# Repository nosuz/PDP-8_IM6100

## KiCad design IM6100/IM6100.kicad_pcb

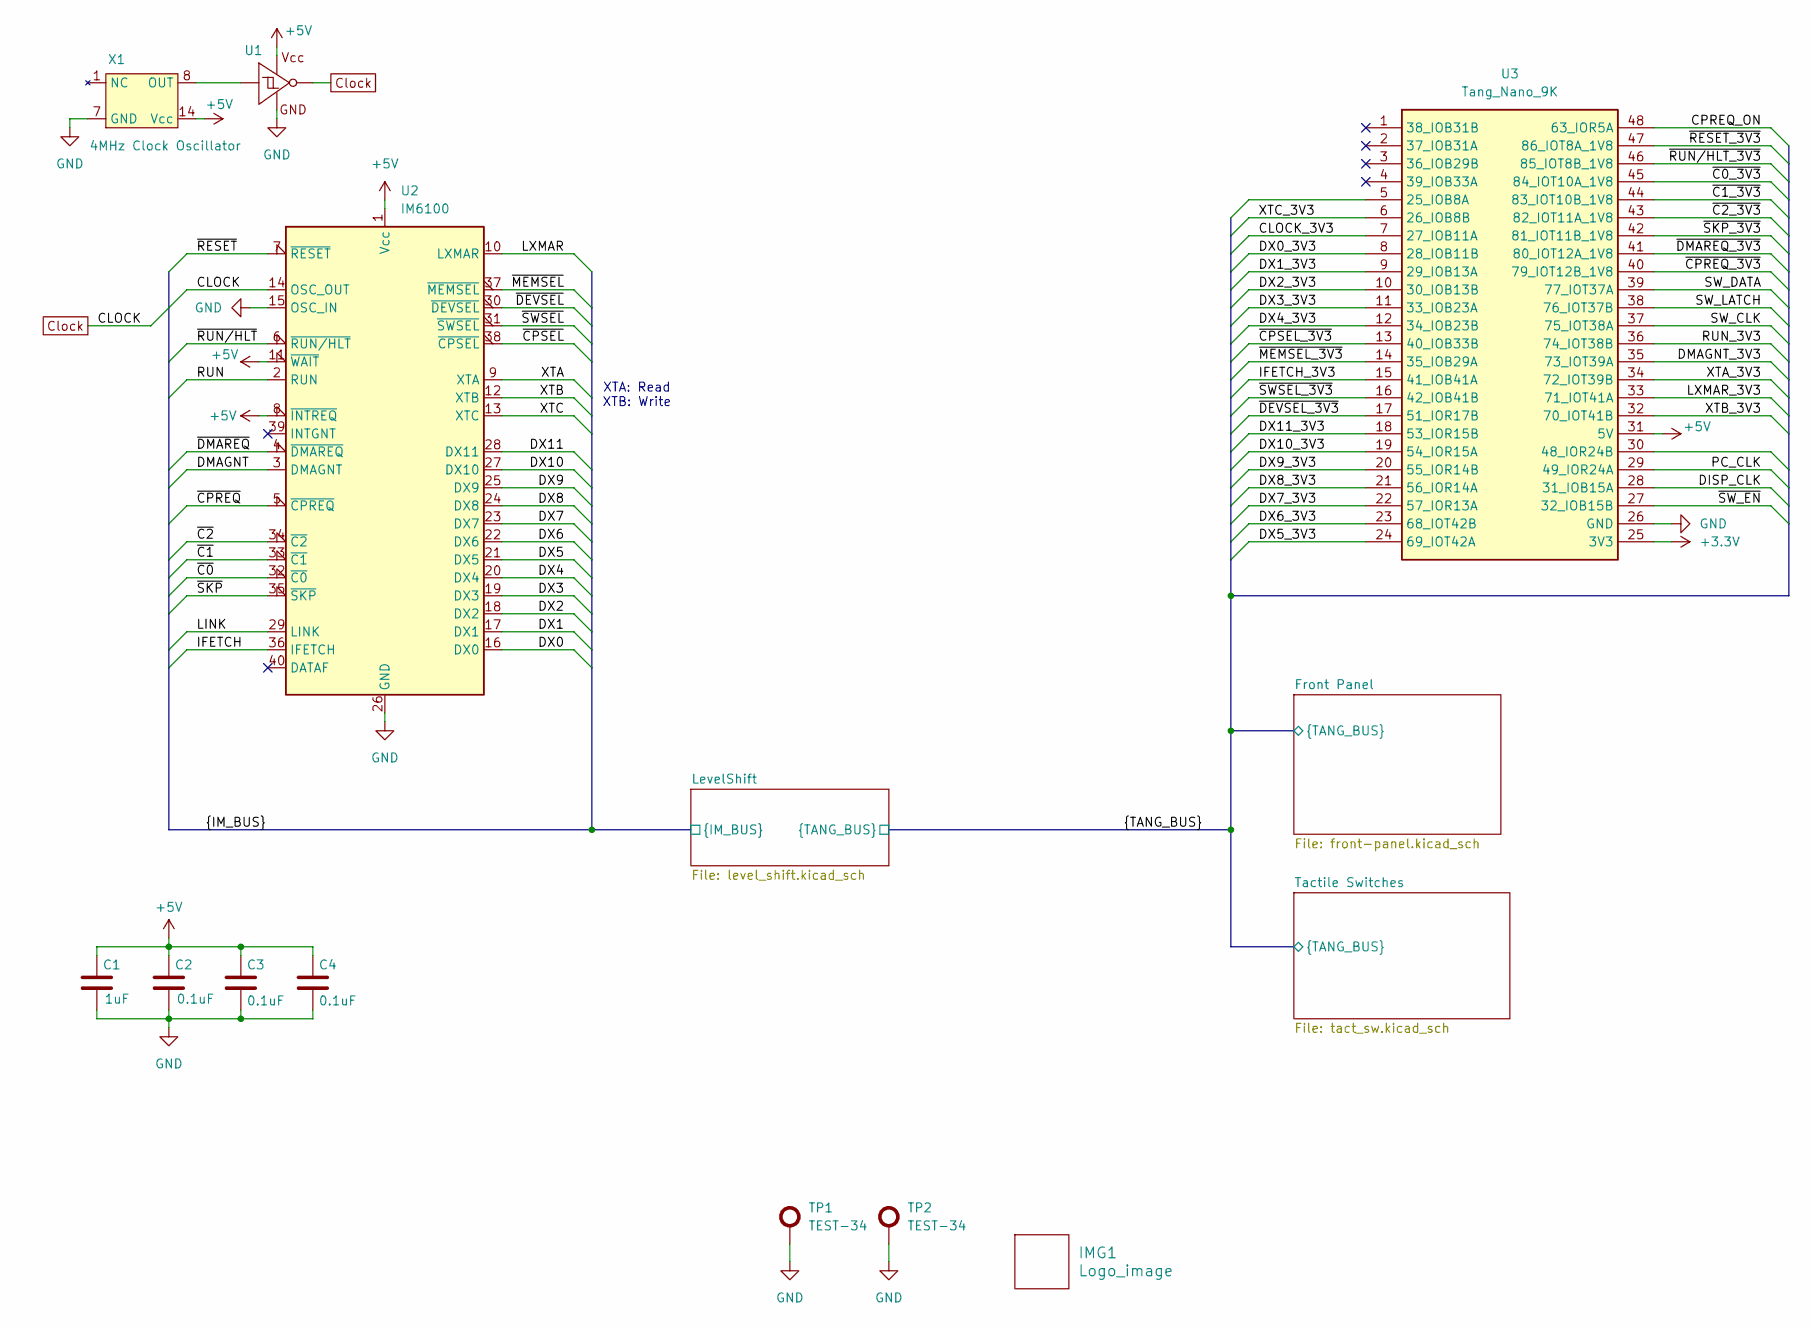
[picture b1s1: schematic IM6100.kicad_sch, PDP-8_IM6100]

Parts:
C1: 1uF; C_1608_0603; LCSC C15849
C2, C3, C4: 0.1uF; C_1608_0603; LCSC C14663
IMG1: Logo_image; Icon_Nosuz
TP1, TP2: TEST-34
U1: SN74AHCT1G14DBV; SOT-23-5_TI; LCSC C55250
U2: IM6100; DIP-40_IM6100
U3: Tang_Nano_9K; DIP-48_TangNano9K
X1: 4MHz Clock Oscillator; DIP-14_ClockOscillator

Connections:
+3.3V: U3.25 (3V3); also elsewhere on the board
+5V: C1.1, C2.1, C3.1, C4.1, U1.5 (Vcc), U2.1 (Vcc), U2.8 (~INTREQ), U2.11 (~WAIT), U3.31 (5V), X1.11 (Vcc), X1.14 (Vcc); also elsewhere on the board
/CLOCK_3V3: U3.7 (27_IOB11A); also elsewhere on the board
/CPREQ_ON: U3.48 (63_IOR5A); also elsewhere on the board
/DISP_CLK: U3.28 (31_IOB15A); also elsewhere on the board
/DMAGNT: U2.3 (DMAGNT); also elsewhere on the board
/DMAGNT_3V3: U3.35 (73_IOT39A); also elsewhere on the board
/DX0: U2.16 (DX0); also elsewhere on the board
/DX0_3V3: U3.8 (28_IOB11B); also elsewhere on the board
/DX1: U2.17 (DX1); also elsewhere on the board
/DX1_3V3: U3.9 (29_IOB13A); also elsewhere on the board
/DX2: U2.18 (DX2); also elsewhere on the board
/DX2_3V3: U3.10 (30_IOB13B); also elsewhere on the board
/DX3: U2.19 (DX3); also elsewhere on the board
/DX3_3V3: U3.11 (33_IOB23A); also elsewhere on the board
/DX4: U2.20 (DX4); also elsewhere on the board
/DX4_3V3: U3.12 (34_IOB23B); also elsewhere on the board
/DX5: U2.21 (DX5); also elsewhere on the board
/DX5_3V3: U3.24 (69_IOT42A); also elsewhere on the board
/DX6: U2.22 (DX6); also elsewhere on the board
/DX6_3V3: U3.23 (68_IOT42B); also elsewhere on the board
/DX7: U2.23 (DX7); also elsewhere on the board
/DX7_3V3: U3.22 (57_IOR13A); also elsewhere on the board
/DX8: U2.24 (DX8); also elsewhere on the board
/DX8_3V3: U3.21 (56_IOR14A); also elsewhere on the board
/DX9: U2.25 (DX9); also elsewhere on the board
/DX9_3V3: U3.20 (55_IOR14B); also elsewhere on the board
/DX10: U2.27 (DX10); also elsewhere on the board
/DX10_3V3: U3.19 (54_IOR15A); also elsewhere on the board
/DX11: U2.28 (DX11); also elsewhere on the board
/DX11_3V3: U3.18 (53_IOR15B); also elsewhere on the board
/IFETCH: U2.36 (IFETCH); also elsewhere on the board
/IFETCH_3V3: U3.15 (41_IOB41A); also elsewhere on the board
/LINK: U2.29 (LINK); also elsewhere on the board
/LXMAR: U2.10 (LXMAR); also elsewhere on the board
/LXMAR_3V3: U3.33 (71_IOT41A); also elsewhere on the board
/PC_CLK: U3.29 (49_IOR24A); also elsewhere on the board
/RUN: U2.2 (RUN); also elsewhere on the board
/RUN_3V3: U3.36 (74_IOT38B); also elsewhere on the board
/SW_CLK: U3.37 (75_IOT38A); also elsewhere on the board
/SW_DATA: U3.39 (77_IOT37A); also elsewhere on the board
/SW_LATCH: U3.38 (76_IOT37B); also elsewhere on the board
/XTA: U2.9 (XTA); also elsewhere on the board
/XTA_3V3: U3.34 (72_IOT39B); also elsewhere on the board
/XTB: U2.12 (XTB); also elsewhere on the board
/XTB_3V3: U3.32 (70_IOT41B); also elsewhere on the board
/XTC: U2.13 (XTC); also elsewhere on the board
/XTC_3V3: U3.6 (26_IOB8B); also elsewhere on the board
/~C0_3V3: U3.45 (84_IOT10A_1V8); also elsewhere on the board
/~C0: U2.32 (~C0); also elsewhere on the board
/~C1_3V3: U3.44 (83_IOT10B_1V8); also elsewhere on the board
/~C1: U2.33 (~C1); also elsewhere on the board
/~C2_3V3: U3.43 (82_IOT11A_1V8); also elsewhere on the board
/~C2: U2.34 (~C2); also elsewhere on the board
/~CPREQ_3V3: U3.40 (79_IOT12B_1V8); also elsewhere on the board
/~CPREQ: U2.5 (~CPREQ); also elsewhere on the board
/~CPSEL_3V3: U3.13 (40_IOB33B); also elsewhere on the board
/~CPSEL: U2.38 (~CPSEL); also elsewhere on the board
/~DEVSEL_3V3: U3.17 (51_IOR17B); also elsewhere on the board
/~DEVSEL: U2.30 (~DEVSEL); also elsewhere on the board
/~DMAREQ_3V3: U3.41 (80_IOT12A_1V8); also elsewhere on the board
/~DMAREQ: U2.4 (~DMAREQ); also elsewhere on the board
/~MEMSEL_3V3: U3.14 (35_IOB29A); also elsewhere on the board
/~MEMSEL: U2.37 (~MEMSEL); also elsewhere on the board
/~RESET_3V3: U3.47 (86_IOT8A_1V8); also elsewhere on the board
/~RESET: U2.7 (~RESET); also elsewhere on the board
/~RUN/HLT_3V3: U3.46 (85_IOT8B_1V8); also elsewhere on the board
/~RUN/HLT: U2.6 (~RUN/HLT); also elsewhere on the board
/~SKP_3V3: U3.42 (81_IOT11B_1V8); also elsewhere on the board
/~SKP: U2.35 (~SKP); also elsewhere on the board
/~SWSEL_3V3: U3.16 (42_IOB41B); also elsewhere on the board
/~SWSEL: U2.31 (~SWSEL); also elsewhere on the board
/~SW_EN: U3.27 (32_IOB15B); also elsewhere on the board
Clock: U1.4 (Y), U2.14 (OSC_OUT); also elsewhere on the board
GND: C1.2, C2.2, C3.2, C4.2, TP1.1 (Test), TP2.1 (Test), U1.3 (GND), U2.15 (OSC_IN), U2.26 (GND), U3.26 (GND), X1.2 (GND), X1.3 (GND), X1.5 (GND), X1.6 (GND), X1.7 (GND), X1.9 (GND), X1.10 (GND), X1.12 (GND), X1.13 (GND); also elsewhere on the board
unnamed: U1.2 (A), X1.8 (OUT)

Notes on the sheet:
XTA: Read XTB: Write

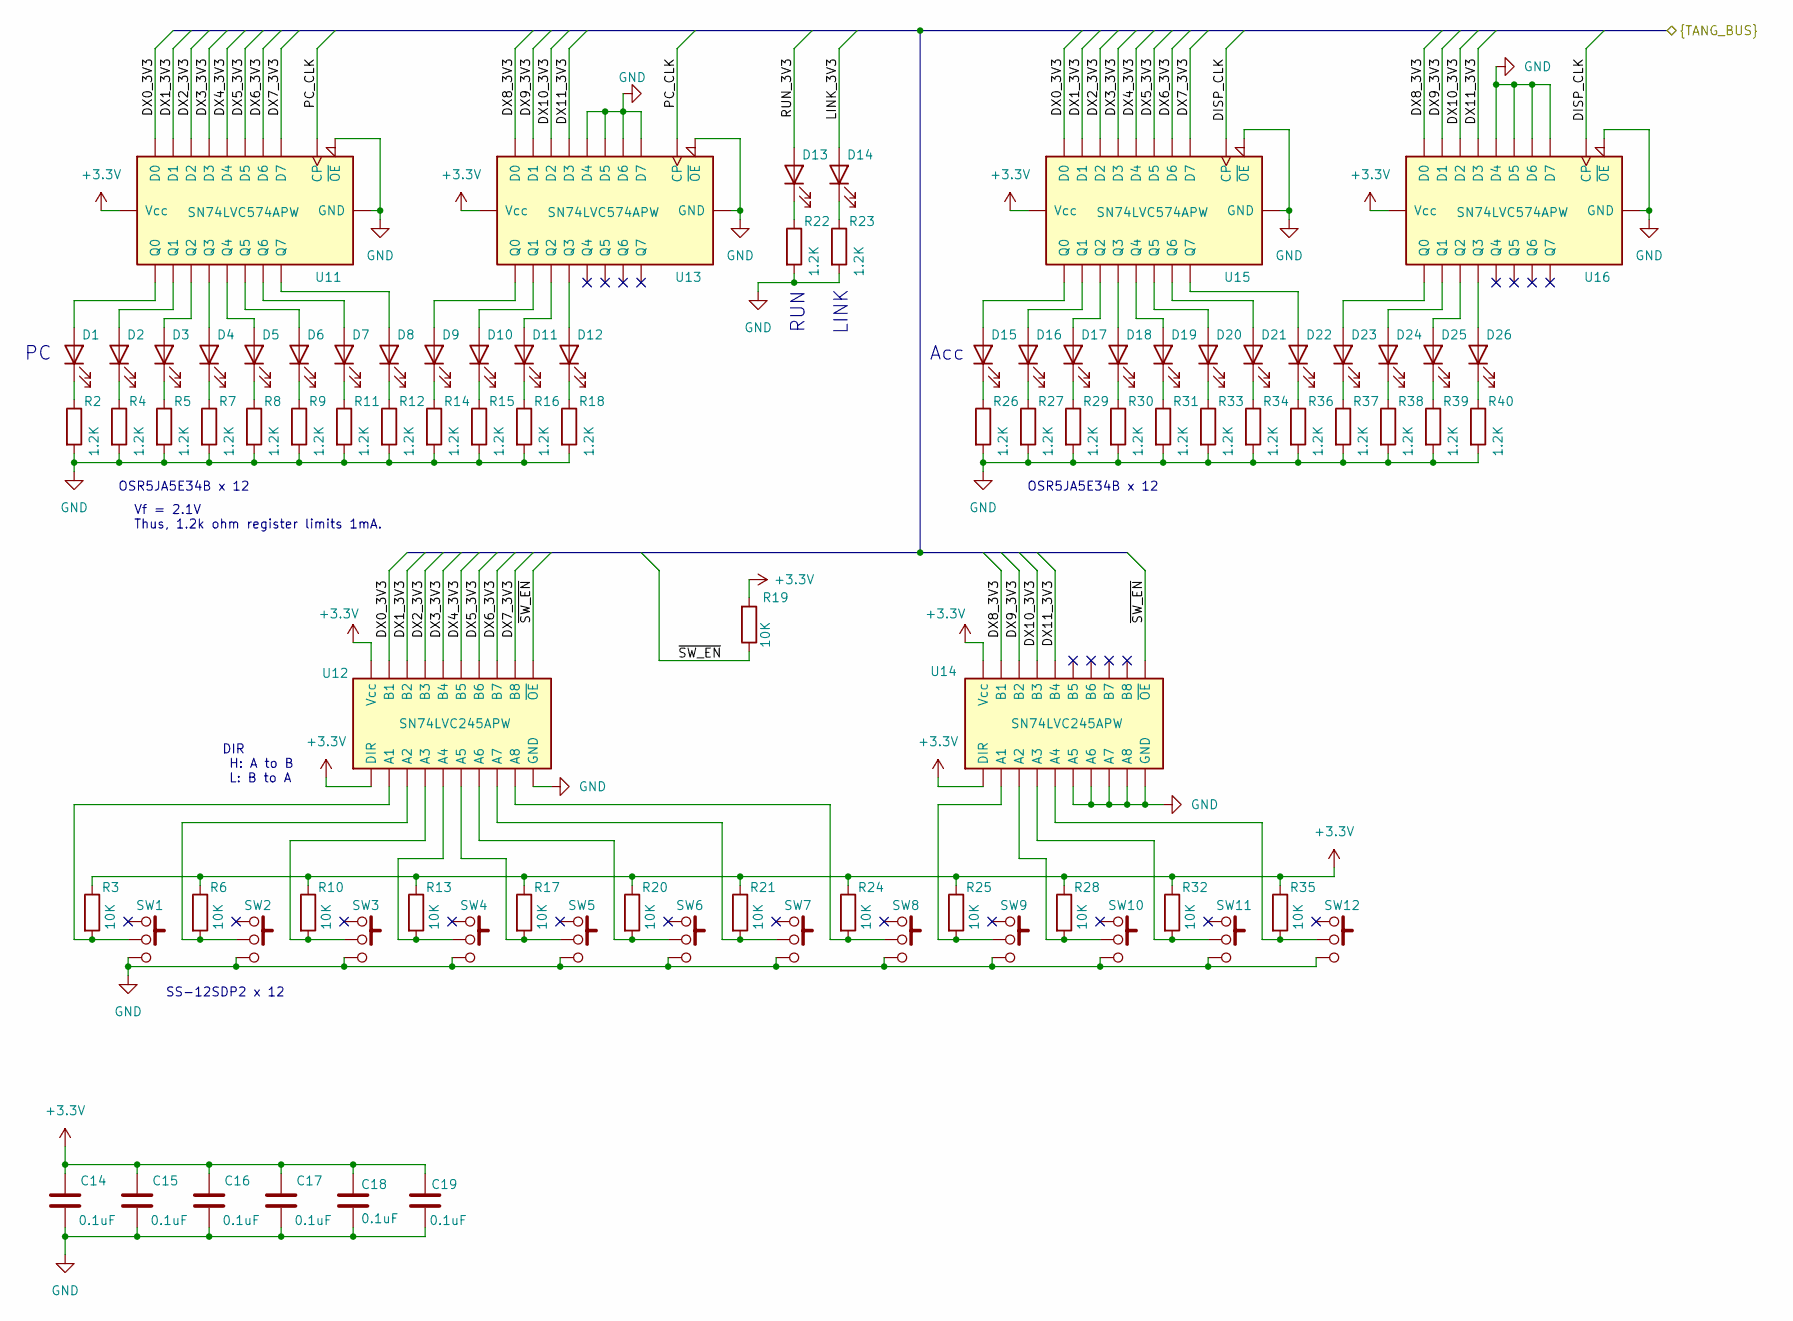
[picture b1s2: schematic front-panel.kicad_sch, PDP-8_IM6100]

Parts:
C14, C15, C16, C17, C18, C19: 0.1uF; C_1608_0603; LCSC C14663
D1, D2, D3, D4, D5, D6, D7, D8, D9, D10, D11, D12, D13, D14, D15, D16, D17, D18, D19, D20, D21, D22, D23, D24, D25, D26: OSR5JA5E34B; LED_5mm
R2, R4, R5, R7, R8, R9, R11, R12, R14, R15, R16, R18, R22, R23, R26, R27, R29, R30, R31, R33, R34, R36, R37, R38, R39, R40: 1.2K; R_1608_0603; LCSC C22765
R3, R6, R10, R13, R17, R19, R20, R21, R24, R25, R28, R32, R35: 10K; R_1608_0603; LCSC C25804
SW1, SW2, SW3, SW4, SW5, SW6, SW7, SW8, SW9, SW10, SW11, SW12: SS-12SDP2
U11, U13, U15, U16: SN74LVC574APW; TSSOP-20_TI-PW; LCSC C7672
U12, U14: SN74LVC245APW; TSSOP-20_TI-PW; LCSC C7848

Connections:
+3.3V: C14.1, C15.1, C16.1, C17.1, C18.1, C19.1, R3.1, R6.1, R10.1, R13.1, R17.1, R19.2, R20.1, R21.1, R24.1, R25.1, R28.1, R32.1, R35.1, U11.20 (Vcc), U12.1 (DIR), U12.20 (Vcc), U13.20 (Vcc), U14.1 (DIR), U14.20 (Vcc), U15.20 (Vcc), U16.20 (Vcc); also elsewhere on the board
/DISP_CLK: U15.11 (CP), U16.11 (CP); also elsewhere on the board
/DX0_3V3: U11.2 (D0), U12.18 (B1), U15.2 (D0); also elsewhere on the board
/DX1_3V3: U11.3 (D1), U12.17 (B2), U15.3 (D1); also elsewhere on the board
/DX2_3V3: U11.4 (D2), U12.16 (B3), U15.4 (D2); also elsewhere on the board
/DX3_3V3: U11.5 (D3), U12.15 (B4), U15.5 (D3); also elsewhere on the board
/DX4_3V3: U11.6 (D4), U12.14 (B5), U15.6 (D4); also elsewhere on the board
/DX5_3V3: U11.7 (D5), U12.13 (B6), U15.7 (D5); also elsewhere on the board
/DX6_3V3: U11.8 (D6), U12.12 (B7), U15.8 (D6); also elsewhere on the board
/DX7_3V3: U11.9 (D7), U12.11 (B8), U15.9 (D7); also elsewhere on the board
/DX8_3V3: U13.2 (D0), U14.18 (B1), U16.2 (D0); also elsewhere on the board
/DX9_3V3: U13.3 (D1), U14.17 (B2), U16.3 (D1); also elsewhere on the board
/DX10_3V3: U13.4 (D2), U14.16 (B3), U16.4 (D2); also elsewhere on the board
/DX11_3V3: U13.5 (D3), U14.15 (B4), U16.5 (D3); also elsewhere on the board
/LINK_3V3: D14.2 (A); also elsewhere on the board
/PC_CLK: U11.11 (CP), U13.11 (CP); also elsewhere on the board
/RUN_3V3: D13.2 (A); also elsewhere on the board
/~SW_EN: R19.1, U12.19 (~OE), U14.19 (~OE); also elsewhere on the board
GND: C14.2, C15.2, C16.2, C17.2, C18.2, C19.2, R2.2, R4.2, R5.2, R7.2, R8.2, R9.2, R11.2, R12.2, R14.2, R15.2, R16.2, R18.2, R22.2, R23.2, R26.2, R27.2, R29.2, R30.2, R31.2, R33.2, R34.2, R36.2, R37.2, R38.2, R39.2, R40.2, SW1.1, SW2.1, SW3.1, SW4.1, SW5.1, SW6.1, SW7.1, SW8.1, SW9.1, SW10.1, SW11.1, SW12.1, U11.1 (~OE), U11.10 (GND), U12.10 (GND), U13.1 (~OE), U13.6 (D4), U13.7 (D5), U13.8 (D6), U13.9 (D7), U13.10 (GND), U14.6 (A5), U14.7 (A6), U14.8 (A7), U14.9 (A8), U14.10 (GND), U15.1 (~OE), U15.10 (GND), U16.1 (~OE), U16.6 (D4), U16.7 (D5), U16.8 (D6), U16.9 (D7), U16.10 (GND); also elsewhere on the board
unnamed: D1.2 (A), U11.19 (Q0)
unnamed: D1.1 (K), R2.1
unnamed: D2.2 (A), U11.18 (Q1)
unnamed: D2.1 (K), R4.1
unnamed: D3.2 (A), U11.17 (Q2)
unnamed: D3.1 (K), R5.1
unnamed: D4.2 (A), U11.16 (Q3)
unnamed: D4.1 (K), R7.1
unnamed: D5.2 (A), U11.15 (Q4)
unnamed: D5.1 (K), R8.1
unnamed: D6.2 (A), U11.14 (Q5)
unnamed: D6.1 (K), R9.1
unnamed: D7.2 (A), U11.13 (Q6)
unnamed: D7.1 (K), R11.1
unnamed: D8.2 (A), U11.12 (Q7)
unnamed: D8.1 (K), R12.1
unnamed: D9.2 (A), U13.19 (Q0)
unnamed: D9.1 (K), R14.1
unnamed: D10.2 (A), U13.18 (Q1)
unnamed: D10.1 (K), R15.1
unnamed: D11.2 (A), U13.17 (Q2)
unnamed: D11.1 (K), R16.1
unnamed: D12.2 (A), U13.16 (Q3)
unnamed: D12.1 (K), R18.1
unnamed: D13.1 (K), R22.1
unnamed: D14.1 (K), R23.1
unnamed: D15.2 (A), U15.19 (Q0)
unnamed: D15.1 (K), R26.1
unnamed: D16.2 (A), U15.18 (Q1)
unnamed: D16.1 (K), R27.1
unnamed: D17.2 (A), U15.17 (Q2)
unnamed: D17.1 (K), R29.1
unnamed: D18.2 (A), U15.16 (Q3)
unnamed: D18.1 (K), R30.1
unnamed: D19.2 (A), U15.15 (Q4)
unnamed: D19.1 (K), R31.1
unnamed: D20.2 (A), U15.14 (Q5)
unnamed: D20.1 (K), R33.1
unnamed: D21.2 (A), U15.13 (Q6)
unnamed: D21.1 (K), R34.1
unnamed: D22.2 (A), U15.12 (Q7)
unnamed: D22.1 (K), R36.1
unnamed: D23.2 (A), U16.19 (Q0)
unnamed: D23.1 (K), R37.1
unnamed: D24.2 (A), U16.18 (Q1)
unnamed: D24.1 (K), R38.1
unnamed: D25.2 (A), U16.17 (Q2)
unnamed: D25.1 (K), R39.1
unnamed: D26.2 (A), U16.16 (Q3)
unnamed: D26.1 (K), R40.1
unnamed: R3.2, SW1.2, U12.2 (A1)
unnamed: R6.2, SW2.2, U12.3 (A2)
unnamed: R10.2, SW3.2, U12.4 (A3)
unnamed: R13.2, SW4.2, U12.5 (A4)
unnamed: R17.2, SW5.2, U12.6 (A5)
unnamed: R20.2, SW6.2, U12.7 (A6)
unnamed: R21.2, SW7.2, U12.8 (A7)
unnamed: R24.2, SW8.2, U12.9 (A8)
unnamed: R25.2, SW9.2, U14.2 (A1)
unnamed: R28.2, SW10.2, U14.3 (A2)
unnamed: R32.2, SW11.2, U14.4 (A3)
unnamed: R35.2, SW12.2, U14.5 (A4)

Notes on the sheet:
OSR5JA5E34B x 12
SS-12SDP2 x 12
Vf = 2.1V Thus, 1.2k ohm register limits 1mA.
LINK
DIR H: A to B L: B to A
RUN
Acc

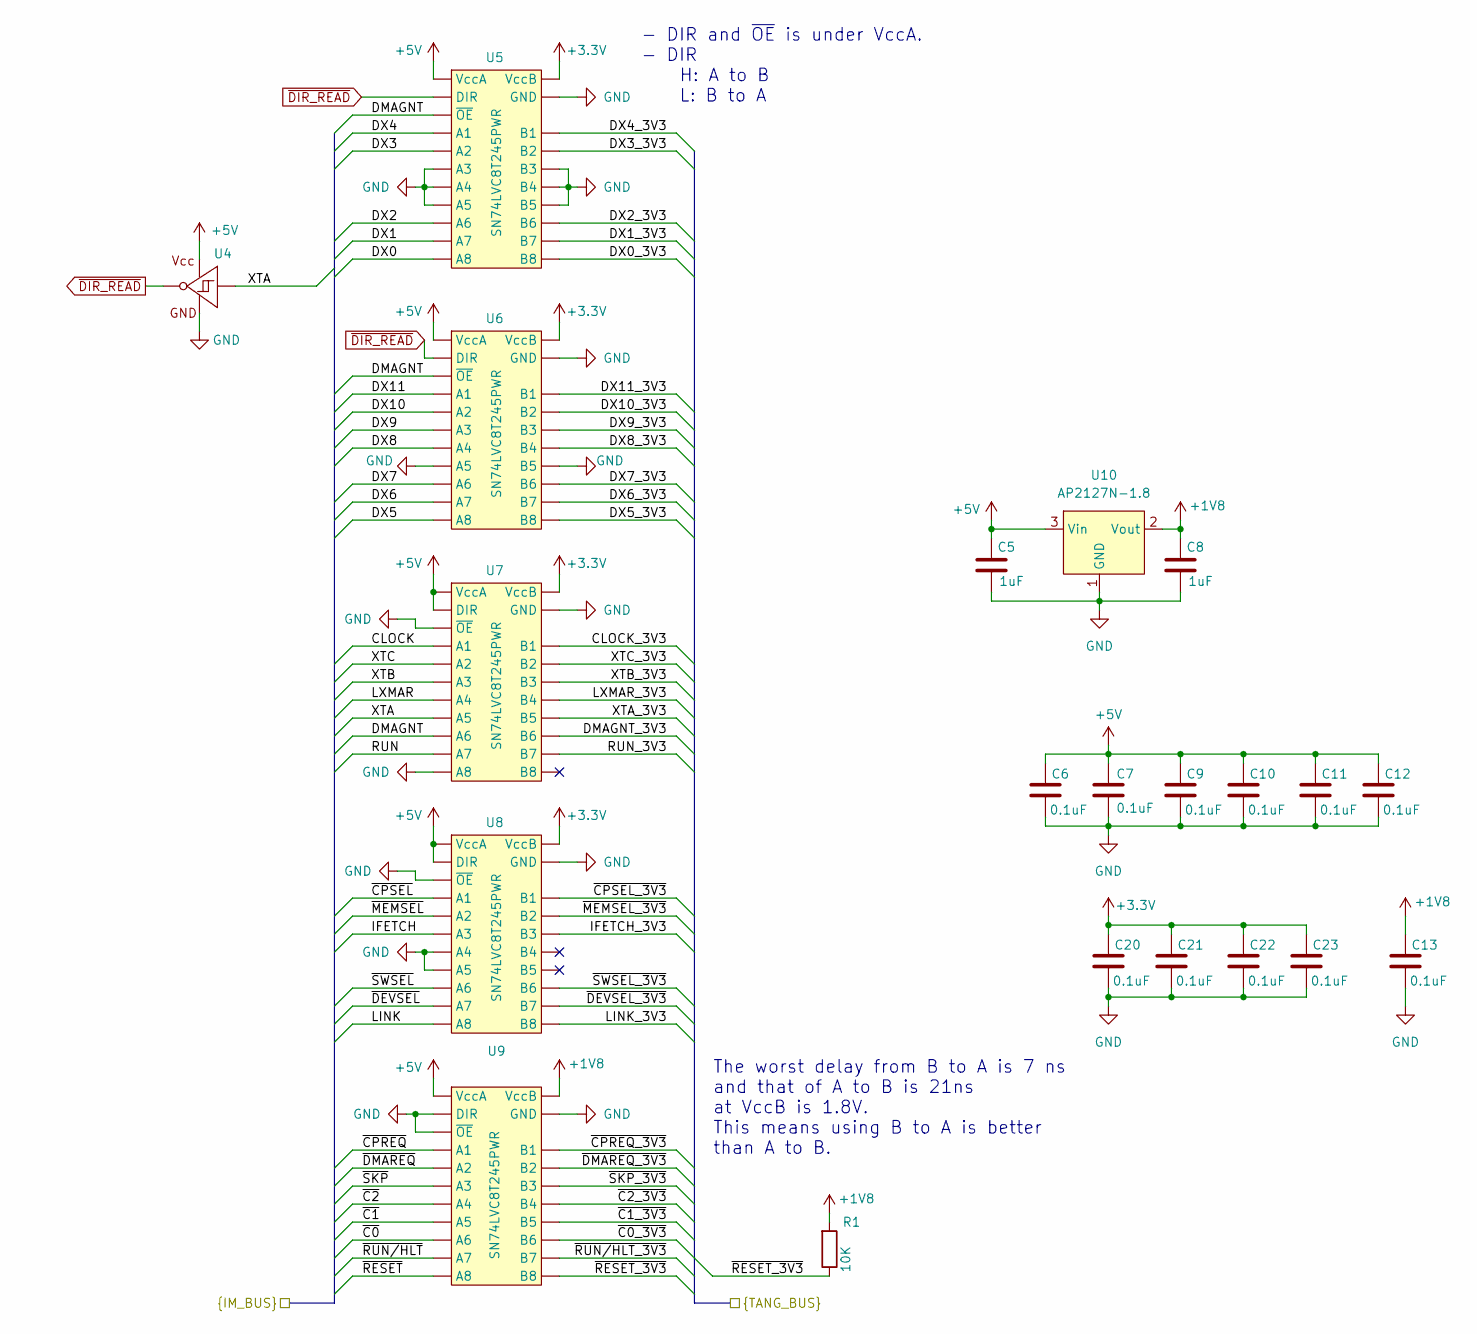
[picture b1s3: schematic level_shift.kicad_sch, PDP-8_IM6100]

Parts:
C5, C8: 1uF; C_1608_0603; LCSC C15849
C6, C7, C9, C10, C11, C12, C13, C20, C21, C22, C23: 0.1uF; C_1608_0603; LCSC C14663
R1: 10K; R_1608_0603; LCSC C25804
U4: SN74AHCT1G14DBV; SOT-23-5_TI; LCSC C55250
U5, U6, U7, U8, U9: SN74LVC8T245PWR; TSSOP-24_TI-PW; LCSC C27643
U10: AP2127N-1.8; SOT-23_AP2127N; LCSC C780749

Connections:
+1V8: C8.1, C13.1, R1.2, U9.23 (VccB), U9.24 (VccB), U10.2 (Vout)
+3.3V: C20.1, C21.1, C22.1, C23.1, U5.23 (VccB), U5.24 (VccB), U6.23 (VccB), U6.24 (VccB), U7.23 (VccB), U7.24 (VccB), U8.23 (VccB), U8.24 (VccB); also elsewhere on the board
+5V: C5.1, C6.1, C7.1, C9.1, C10.1, C11.1, C12.1, U4.5 (Vcc), U5.1 (VccA), U6.1 (VccA), U7.1 (VccA), U7.2 (DIR), U8.1 (VccA), U8.2 (DIR), U9.1 (VccA), U10.3 (Vin); also elsewhere on the board
/CLOCK_3V3: U7.21 (B1); also elsewhere on the board
/DMAGNT: U5.22 (~OE), U6.22 (~OE), U7.8 (A6); also elsewhere on the board
/DMAGNT_3V3: U7.16 (B6); also elsewhere on the board
/DX0: U5.10 (A8); also elsewhere on the board
/DX0_3V3: U5.14 (B8); also elsewhere on the board
/DX1: U5.9 (A7); also elsewhere on the board
/DX1_3V3: U5.15 (B7); also elsewhere on the board
/DX2: U5.8 (A6); also elsewhere on the board
/DX2_3V3: U5.16 (B6); also elsewhere on the board
/DX3: U5.4 (A2); also elsewhere on the board
/DX3_3V3: U5.20 (B2); also elsewhere on the board
/DX4: U5.3 (A1); also elsewhere on the board
/DX4_3V3: U5.21 (B1); also elsewhere on the board
/DX5: U6.10 (A8); also elsewhere on the board
/DX5_3V3: U6.14 (B8); also elsewhere on the board
/DX6: U6.9 (A7); also elsewhere on the board
/DX6_3V3: U6.15 (B7); also elsewhere on the board
/DX7: U6.8 (A6); also elsewhere on the board
/DX7_3V3: U6.16 (B6); also elsewhere on the board
/DX8: U6.6 (A4); also elsewhere on the board
/DX8_3V3: U6.18 (B4); also elsewhere on the board
/DX9: U6.5 (A3); also elsewhere on the board
/DX9_3V3: U6.19 (B3); also elsewhere on the board
/DX10: U6.4 (A2); also elsewhere on the board
/DX10_3V3: U6.20 (B2); also elsewhere on the board
/DX11: U6.3 (A1); also elsewhere on the board
/DX11_3V3: U6.21 (B1); also elsewhere on the board
/IFETCH: U8.5 (A3); also elsewhere on the board
/IFETCH_3V3: U8.19 (B3); also elsewhere on the board
/LINK: U8.10 (A8); also elsewhere on the board
/LINK_3V3: U8.14 (B8); also elsewhere on the board
/LXMAR: U7.6 (A4); also elsewhere on the board
/LXMAR_3V3: U7.18 (B4); also elsewhere on the board
/RUN: U7.9 (A7); also elsewhere on the board
/RUN_3V3: U7.15 (B7); also elsewhere on the board
/XTA: U4.2 (A), U7.7 (A5); also elsewhere on the board
/XTA_3V3: U7.17 (B5); also elsewhere on the board
/XTB: U7.5 (A3); also elsewhere on the board
/XTB_3V3: U7.19 (B3); also elsewhere on the board
/XTC: U7.4 (A2); also elsewhere on the board
/XTC_3V3: U7.20 (B2); also elsewhere on the board
/~C0_3V3: U9.16 (B6); also elsewhere on the board
/~C0: U9.8 (A6); also elsewhere on the board
/~C1_3V3: U9.17 (B5); also elsewhere on the board
/~C1: U9.7 (A5); also elsewhere on the board
/~C2_3V3: U9.18 (B4); also elsewhere on the board
/~C2: U9.6 (A4); also elsewhere on the board
/~CPREQ_3V3: U9.21 (B1); also elsewhere on the board
/~CPREQ: U9.3 (A1); also elsewhere on the board
/~CPSEL_3V3: U8.21 (B1); also elsewhere on the board
/~CPSEL: U8.3 (A1); also elsewhere on the board
/~DEVSEL_3V3: U8.15 (B7); also elsewhere on the board
/~DEVSEL: U8.9 (A7); also elsewhere on the board
/~DMAREQ_3V3: U9.20 (B2); also elsewhere on the board
/~DMAREQ: U9.4 (A2); also elsewhere on the board
/~MEMSEL_3V3: U8.20 (B2); also elsewhere on the board
/~MEMSEL: U8.4 (A2); also elsewhere on the board
/~RESET_3V3: R1.1, U9.14 (B8); also elsewhere on the board
/~RESET: U9.10 (A8); also elsewhere on the board
/~RUN/HLT_3V3: U9.15 (B7); also elsewhere on the board
/~RUN/HLT: U9.9 (A7); also elsewhere on the board
/~SKP_3V3: U9.19 (B3); also elsewhere on the board
/~SKP: U9.5 (A3); also elsewhere on the board
/~SWSEL_3V3: U8.16 (B6); also elsewhere on the board
/~SWSEL: U8.8 (A6); also elsewhere on the board
Clock: U7.3 (A1); also elsewhere on the board
GND: C5.2, C6.2, C7.2, C8.2, C9.2, C10.2, C11.2, C12.2, C13.2, C20.2, C21.2, C22.2, C23.2, U4.3 (GND), U5.5 (A3), U5.6 (A4), U5.7 (A5), U5.11 (GND), U5.12 (GND), U5.13 (GND), U5.17 (B5), U5.18 (B4), U5.19 (B3), U6.7 (A5), U6.11 (GND), U6.12 (GND), U6.13 (GND), U6.17 (B5), U7.10 (A8), U7.11 (GND), U7.12 (GND), U7.13 (GND), U7.22 (~OE), U8.6 (A4), U8.7 (A5), U8.11 (GND), U8.12 (GND), U8.13 (GND), U8.22 (~OE), U9.2 (DIR), U9.11 (GND), U9.12 (GND), U9.13 (GND), U9.22 (~OE), U10.1 (GND); also elsewhere on the board
~DIR_READ: U4.4 (Y), U5.2 (DIR), U6.2 (DIR)

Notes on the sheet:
The worst delay from B to A is 7 ns and that of A to B is 21ns at VccB is 1.8V. This means using B to A is better than A to B.
- DIR and ~{OE} is under VccA. - DIR H: A to B L: B to A

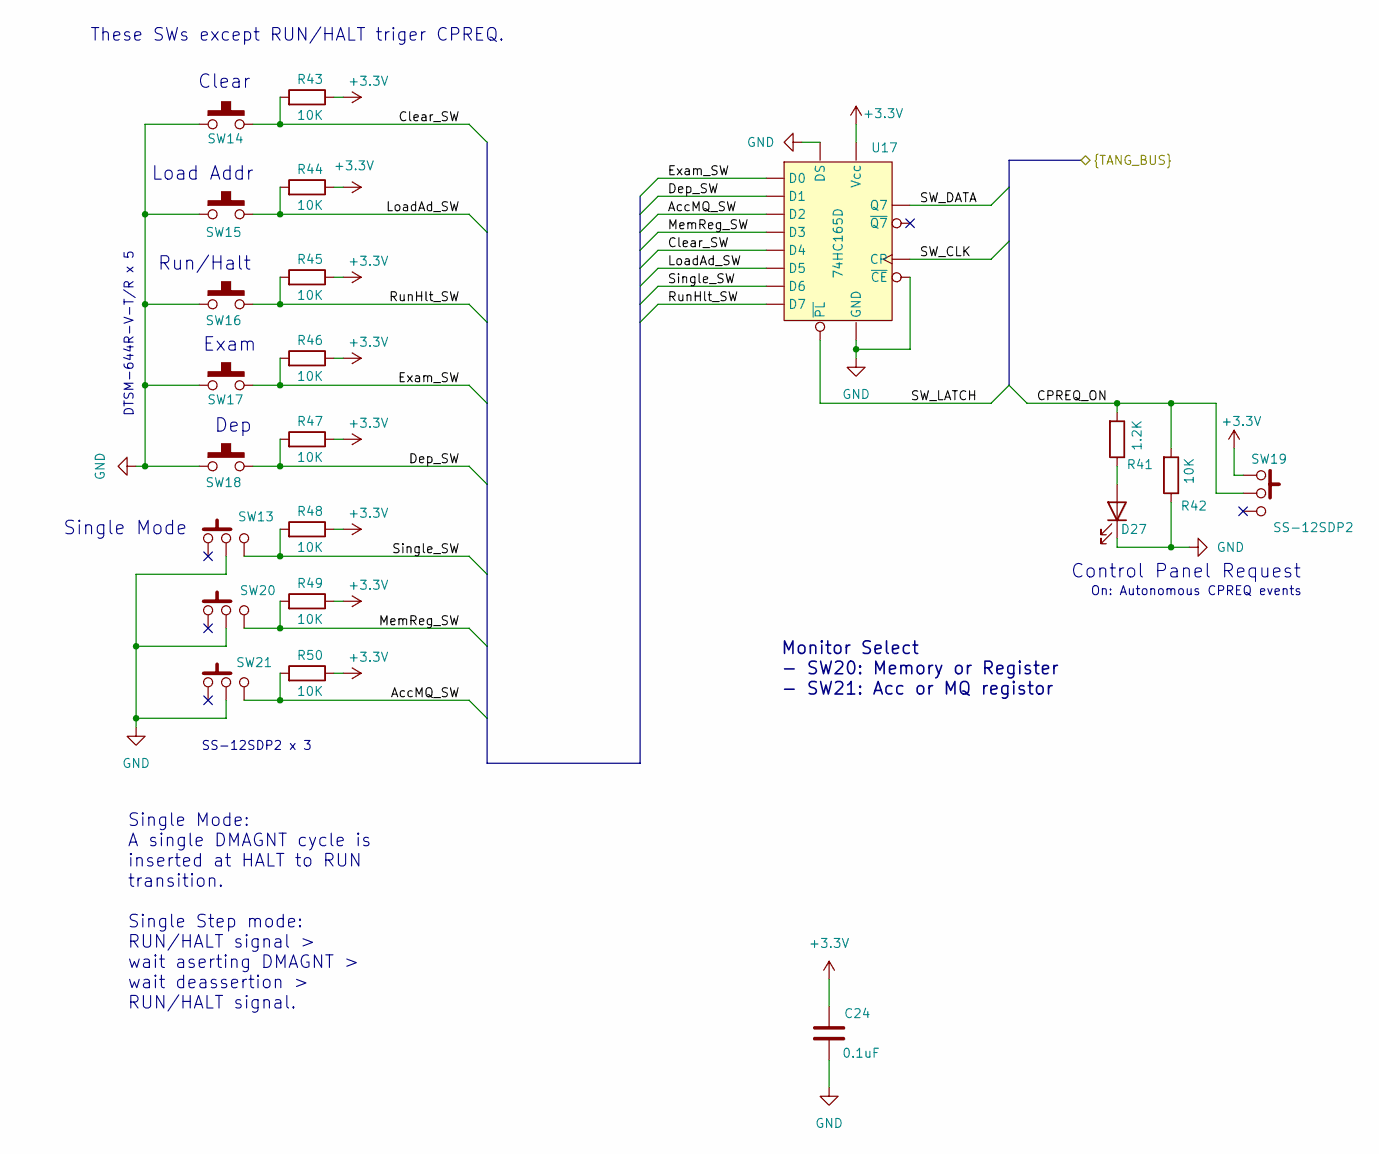
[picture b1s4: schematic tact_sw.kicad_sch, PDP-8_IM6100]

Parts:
C24: 0.1uF; C_1608_0603; LCSC C14663
D27: OSR5JA5E34B; LED_5mm
R41: 1.2K; R_1608_0603; LCSC C22765
R42, R43, R44, R45, R46, R47, R48, R49, R50: 10K; R_1608_0603; LCSC C25804
SW13, SW19, SW20, SW21: SS-12SDP2
SW14, SW15, SW16, SW17, SW18: DTSM-63N-V-T/R; DTSM-6x; LCSC C133973
U17: 74HC165D; SOIC-16_3.9x9.9mm_P1.27mm; LCSC C5613

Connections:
+3.3V: C24.1, R43.1, R44.1, R45.1, R46.1, R47.1, R48.1, R49.1, R50.1, SW19.3, U17.16 (Vcc); also elsewhere on the board
/CPREQ_ON: R41.2, R42.2, SW19.2; also elsewhere on the board
/SW_CLK: U17.2 (CP); also elsewhere on the board
/SW_DATA: U17.9 (Q7); also elsewhere on the board
/SW_LATCH: U17.1 (~PL); also elsewhere on the board
/Tactile Switches/AccMQ_SW: R50.2, SW21.1, U17.13 (D2)
/Tactile Switches/Clear_SW: R43.2, SW14.3 (C), SW14.4 (D), U17.3 (D4)
/Tactile Switches/Dep_SW: R47.2, SW18.3 (C), SW18.4 (D), U17.12 (D1)
/Tactile Switches/Exam_SW: R46.2, SW17.3 (C), SW17.4 (D), U17.11 (D0)
/Tactile Switches/LoadAd_SW: R44.2, SW15.3 (C), SW15.4 (D), U17.4 (D5)
/Tactile Switches/MemReg_SW: R49.2, SW20.1, U17.14 (D3)
/Tactile Switches/RunHlt_SW: R45.2, SW16.3 (C), SW16.4 (D), U17.6 (D7)
/Tactile Switches/Single_SW: R48.2, SW13.1, U17.5 (D6)
GND: C24.2, D27.1 (K), R42.1, SW13.2, SW14.1 (A), SW14.2 (B), SW15.1 (A), SW15.2 (B), SW16.1 (A), SW16.2 (B), SW17.1 (A), SW17.2 (B), SW18.1 (A), SW18.2 (B), SW20.2, SW21.2, U17.8 (GND), U17.10 (DS), U17.15 (~CE); also elsewhere on the board
unnamed: D27.2 (A), R41.1

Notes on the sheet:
Load Addr
Single Mode
Run/Halt
Dep
Single Mode: A single DMAGNT cycle is inserted at HALT to RUN transition. Single Step mode: RUN/HALT signal > wait aserting DMAGNT > wait deassertion > RUN/HALT signal.
Clear
Control Panel Request
Monitor Select - SW20: Memory or Register - SW21: Acc or MQ registor
These SWs except RUN/HALT triger CPREQ.
SS-12SDP2 x 3
DTSM-644R-V-T/R x 5
On: Autonomous CPREQ events
Exam

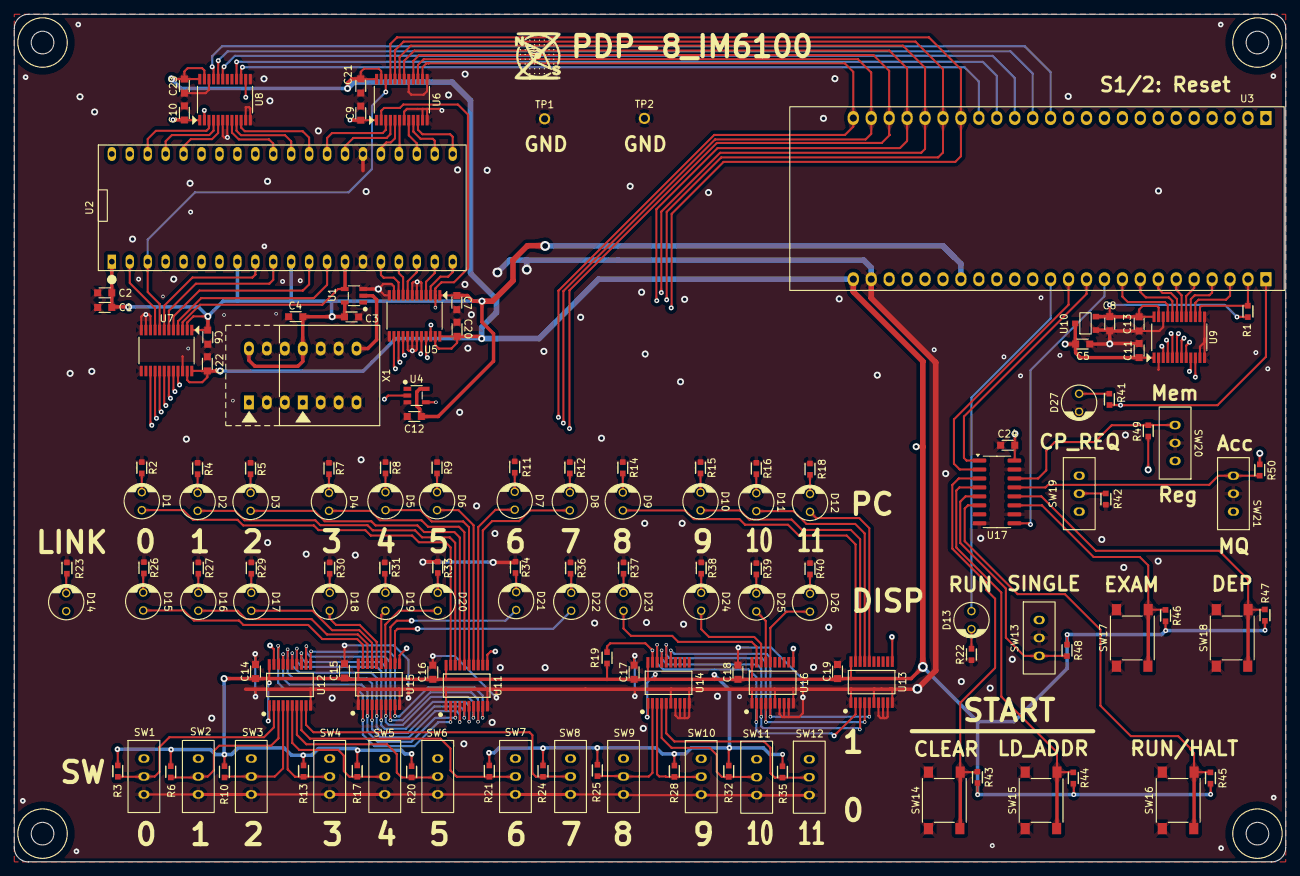
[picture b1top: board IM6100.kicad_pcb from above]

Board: 4 copper layers, 180.0 x 120.0 mm, 143 parts (0 on the bottom side), 150 nets.

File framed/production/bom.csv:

Designator,Footprint,Quantity,Value,LCSC Part #,Akizuki Part #
"C1, C5, C8",C_1608_0603,3,1uF,C15849,
"C10, C11, C12, C13, C14, C15, C16, C17, C18, C19, C2, C20, C21, C22, C23, C24, C3, C4, C6, C7, C9",C_1608_0603,21,0.1uF,C14663,
"D1, D10, D11, D12, D13, D14, D15, D16, D17, D18, D19, D2, D20, D21, D22, D23, D24, D25, D26, D27, D3, D4, D5, D6, D7, D8, D9",LED_5mm,27,OSR5JA5E34B,,"112605
(10個入り116588)"
"R1, R10, R13, R17, R19, R20, R21, R24, R25, R28, R3, R32, R35, R42, R43, R44, R45, R46, R47, R48, R49, R50, R6",R_1608_0603,23,10K,C25804,
"R11, R12, R14, R15, R16, R18, R2, R22, R23, R26, R27, R29, R30, R31, R33, R34, R36, R37, R38, R39, R4, R40, R41, R5, R7, R8, R9",R_1608_0603,27,1.2K,C22765,
"SW1, SW10, SW11, SW12, SW13, SW19, SW2, SW20, SW21, SW3, SW4, SW5, SW6, SW7, SW8, SW9",SS-12SDP2,16,SS-12SDP2,C5189013,115643
"SW14, SW15, SW16, SW17, SW18",DTSM-6x,5,DTSM-63N-V-T/R,C133973,
"TP1, TP2",TEST-34,2,TEST-34,,112217
"U1, U4",SOT-23-5_TI,2,SN74AHCT1G14DBV,C55250,
U10,SOT-23_AP2127N,1,AP2127N-1.8,C780749,
"U11, U13, U15, U16",TSSOP-20_TI-PW,4,SN74LVC574APW,C7672,
"U12, U14",TSSOP-20_TI-PW,2,SN74LVC245APW,C7848,
U17,SOIC-16_3.9x9.9mm_P1.27mm,1,74HC165D,C5613,
U2,DIP-40_IM6100,1,IM6100,,IC socket: 100034
U3,DIP-48_TangNano9K,1,Tang_Nano_9K,,"117448
IC socket: 101591 x 2
Connector: 101382 x 2"
"U5, U6, U7, U8, U9",TSSOP-24_TI-PW,5,SN74LVC8T245PWR,C27643,
X1,DIP-14_ClockOscillator,1,4MHz Clock Oscillator,,"101567 (3.5MHz)
117019 (1MHz)"

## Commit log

2025-09-10 init
2025-09-10 Created KiCad project.
2025-09-11 Updated .gitignore to ignore Libreoffice and KiCad crash backup files.
2025-09-13 Updated .gitignore.
2025-09-13 Updated symbol and footprint module.
2025-09-14 PCB for IM6100, PDP-8 ISA compatible 12 bit microprocessor.
2025-09-14 Removed Pull-dow on ~RESET.
    TXB0108 can't use pull-up and -down.
2025-09-14 Fixed to reset IM6100 during setting up Tang Nano 9K.
2025-09-14 Updated tactile switch.
2025-09-15 Updated IC socket part number for IM6100.
2025-10-13 Updated BOM file.
2025-10-13 Added a simple Veryl study code.
2025-11-16 Replaced level shifter logics to SN74LVC8T245.
